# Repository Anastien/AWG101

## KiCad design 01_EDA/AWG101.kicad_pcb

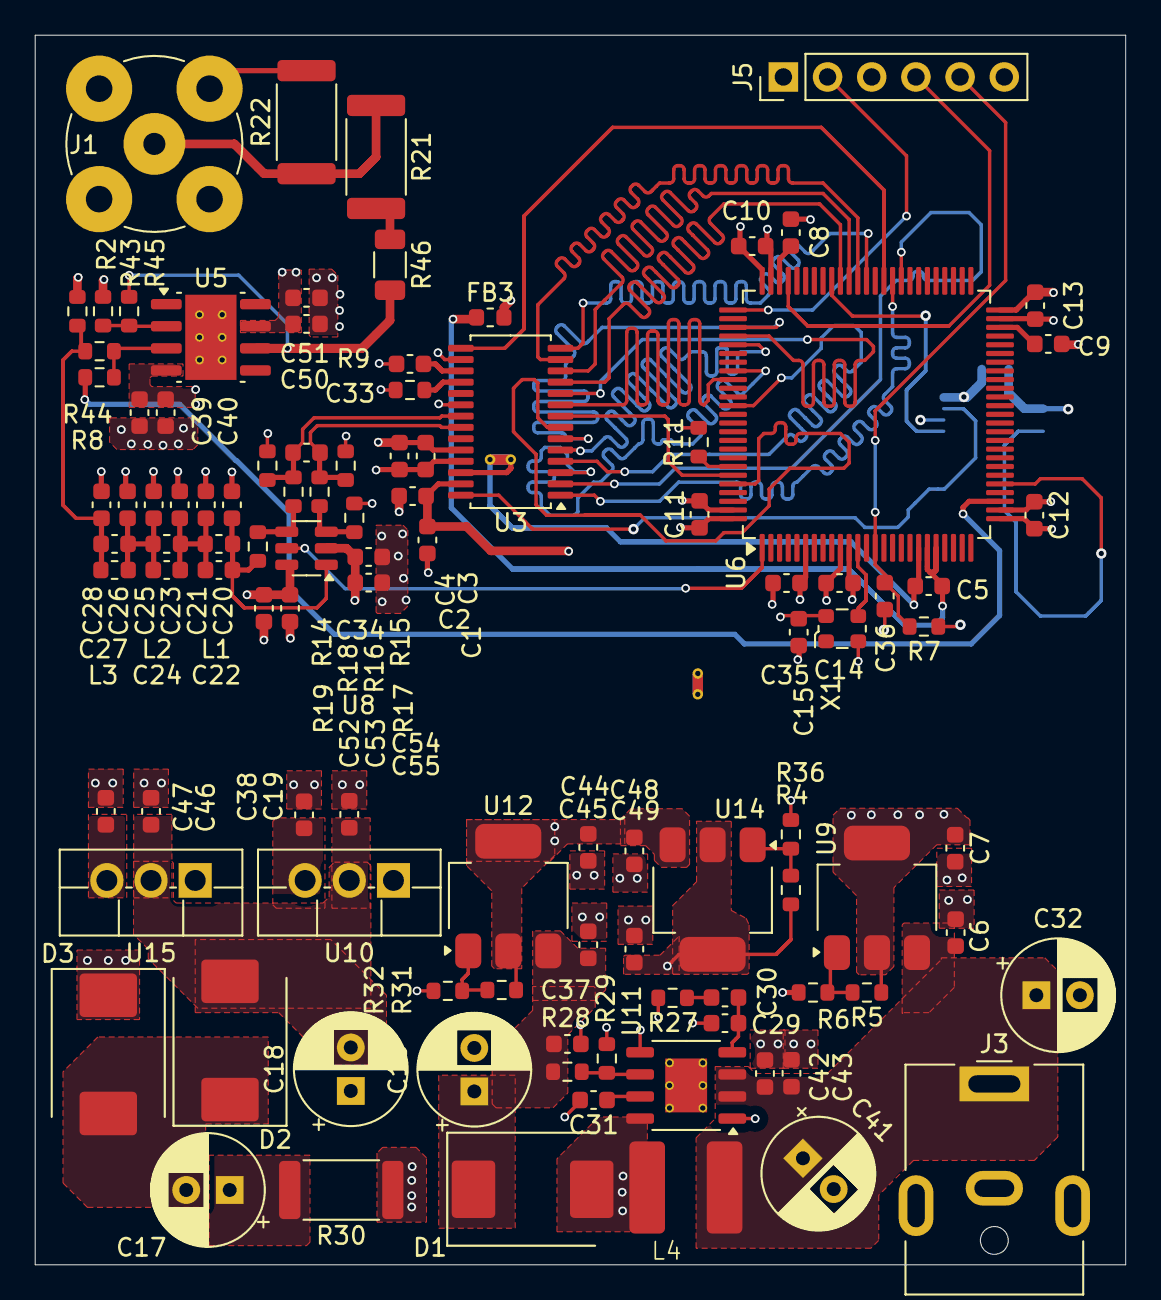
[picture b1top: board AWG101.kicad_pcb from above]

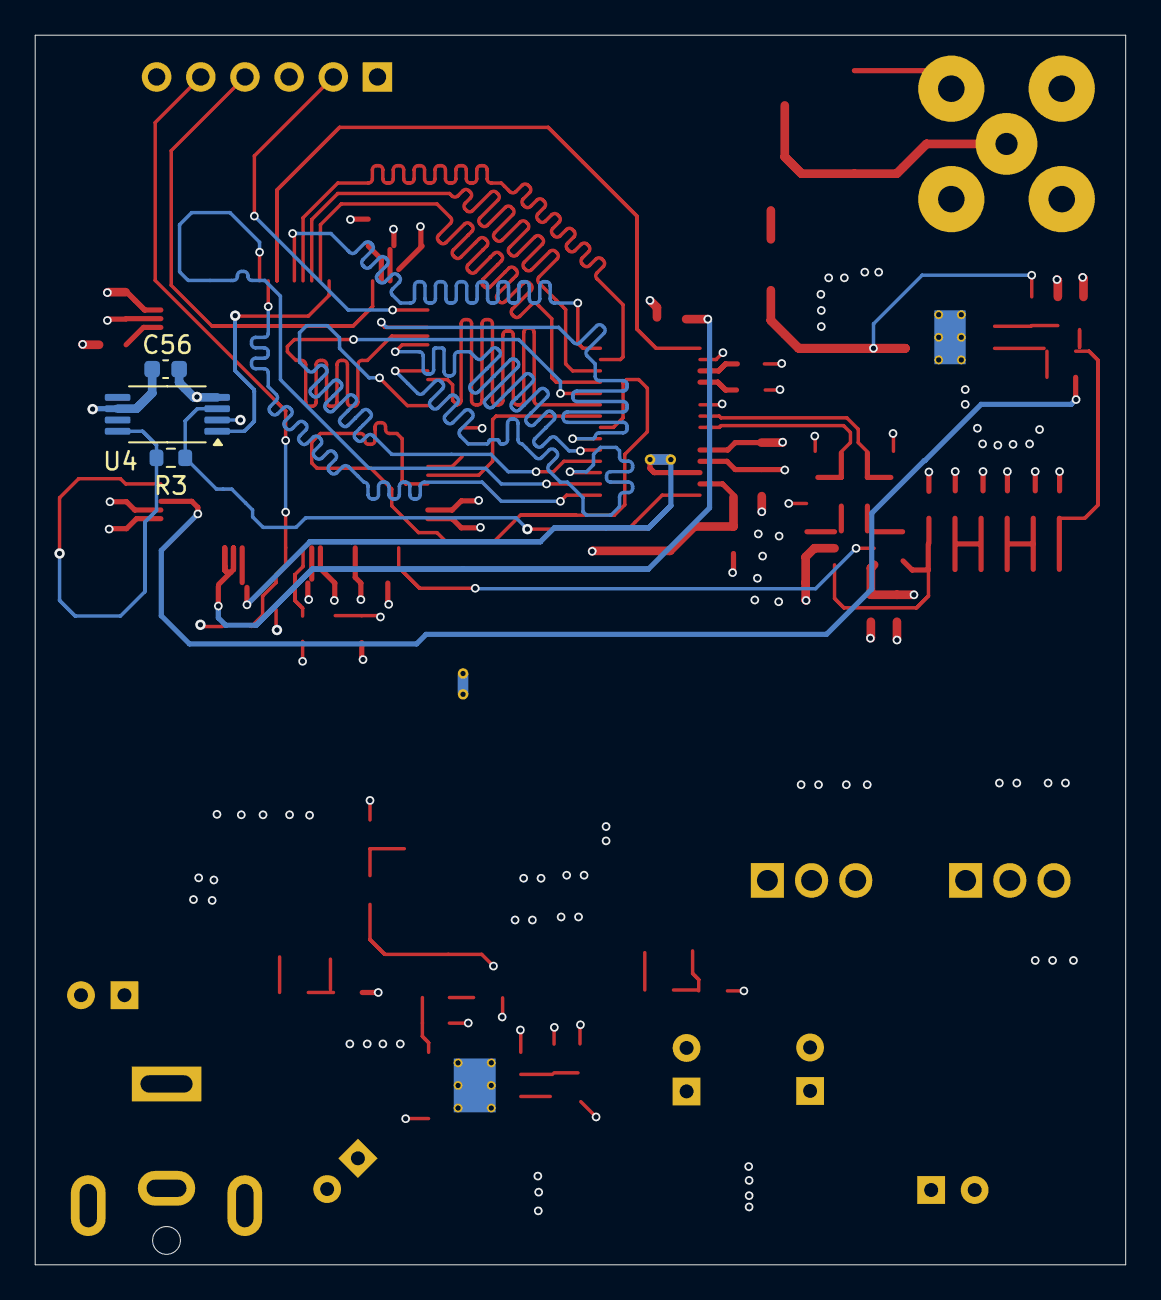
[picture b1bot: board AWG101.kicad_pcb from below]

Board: 4 copper layers, 62.7 x 70.7 mm, 109 parts (3 on the bottom side), 64 nets.

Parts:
C1, C2, C3, C4, C8, C9: 2.2U; C_0603_1608Metric
C5, C35: 4.7U; C_0603_1608Metric
C6, C7, C19, C37, C38, C39, C40, C42, C44, C45, C46, C47, C48, C49, C50, C51, C52, C53, C54, C55: 10u; C_0603_1608Metric
C10, C11, C12, C13, C14, C15, C36, C56: 0.1U; C_0603_1608Metric
C16, C17, C18, C32, C41: 120u; CP_Radial_D6.3mm_P2.50mm
C20, C28: 22pF; C_0603_1608Metric
C21, C25: 27pF; C_0603_1608Metric
C22, C24, C27: 9.1pF; C_0603_1608Metric
C23, C26: 91pF; C_0603_1608Metric
C29: 47p; C_0603_1608Metric
C30: 2.2n; C_0603_1608Metric
C31: 10n; C_0603_1608Metric
C33: 4.5pF; C_0603_1608Metric
C34: 10nF; C_0603_1608Metric
C43: 1u; C_0603_1608Metric
D1, D2, D3: SS34; D_SMC
FB3: FerriteBead; L_0603_1608Metric
J1: 112404; BNC_TEConnectivity_1478204_Vertical
J3: Jack-DC; BarrelJack_CUI_PJ-063AH_Horizontal
J5: PinHeader_1x06_P2.54mm_Vertical
L1, L3: 150nH; L_0603_1608Metric
L2: 250nH; L_0603_1608Metric
L4: 6.8u; OWINR6045-6R8
NT1, NT2: NetTie_2; NetTie-2_THT_Pad0.3mm
R2, R8, R17, R43, R44, R45: 35.7; R_0603_1608Metric
R3: 0; R_0603_1608Metric
R4, R6, R29, R32: 10k; R_0603_1608Metric
R5: 6.04k; R_0603_1608Metric
R7, R11: 10K; R_0603_1608Metric
R9: 49.9; R_0603_1608Metric
R14: 31.6; R_0603_1608Metric
R15: 53.6; R_0603_1608Metric
R16: 10.7; R_0603_1608Metric
R18: 221; R_0603_1608Metric
R19: 402; R_0603_1608Metric
R21, R22: 35.7; R_2512_6332Metric
R27: 51k; R_0603_1608Metric
R28: 93.1k; R_0603_1608Metric
R30: 1; R_2512_6332Metric
R31: 1.15k; R_0603_1608Metric
R36: 3.3k; R_0603_1608Metric
R46: 35.7; R_1206_3216Metric
U3: MXT2144; TSSOP-28_4.4x9.7mm_P0.65mm
U4: TSSOP-8_4.4x3mm_P0.65mm
U5: THS3095DDA; Texas_R-PDSO-G8_EP2.95x4.9mm_Mask2.4x3.1mm_ThermalVias
U6: STM32H723VGT6; LQFP-100_14x14mm_P0.5mm
U8: OPA695IDBVR; SOT-23-6
U9, U12, U14: LM1117MP-ADJ; SOT-223-3_TabPin2
U10: L7905; TO-220F-3_Vertical
U11: PAM2421AECADJR; HSOP-8-1EP_3.9x4.9mm_P1.27mm_EP2.41x3.1mm_ThermalVias
U15: L7912; TO-220F-3_Vertical
X1: ECS-TXO-2520MV-100-AN-TR; Oscillator_SMD_ECS_2520MV-xxx-xx-4Pin_2.5x2.0mm

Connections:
+3.3VLDO: C1.1, C2.1, C7.1, C10.1, C11.1, C12.1, C13.1, C14.1, C15.1, C35.1, C56.1, FB3.2, J5.1 (VDD), R5.1, R7.1, U3.27 (DVDD), U4.2 (1G), U4.6 (V_{DD}), U6.6 (VBAT), U6.11 (VDD), U6.27 (VDD), U6.50 (VDD), U6.75 (VDD), U6.100 (VDD), U9.2 (VO), X1.4 (VDD)
+3V3A: C3.1, C4.1, C5.1, FB3.1, U3.24 (AVDD), U6.20 (VREF+), U6.21 (VDDA)
+5VLDO: C49.1, C52.1, C53.1, R36.1, U8.6 (V+), U14.2 (VO)
+12VLDO: C45.1, C48.1, C50.1, C51.1, R31.1, U5.7 (V+), U12.2 (VO), U14.3 (VI)
+13V: C16.1, C37.1, C44.1, D1.1 (K), R28.1, U12.3 (VI)
-5V_LDO: C38.2, C54.1, C55.1, U8.2 (V-), U10.3 (VO)
-12V_LDO: C39.1, C40.1, C47.2, U5.4 (V-), U15.3 (VO)
-13V: C18.2, C19.2, C46.2, D3.2 (A), U10.2 (VI), U15.2 (VI)
/AWG/10MHZ: U6.12 (PH0), X1.3 (OUT)
/AWG/695_EN: U6.1 (PE2), U8.5 (~DIS)
/AWG/2421_SW: D1.2 (A), L4.2, R30.1, U11.8 (SW)
/AWG/DAC_CLK: R3.1, U3.28 (CLK), U4.3 (Y0)
/AWG/DAC_EN: U3.15 (SLEEP), U6.61 (PD14)
/AWG/DAC_SE: C20.1, C22.1, L1.1, R19.1, U8.1
/AWG/DAC_SE_FLT: C27.2, C28.1, L3.2, R2.1, R44.2
/AWG/IOUT_N: C34.1, R14.1, R18.2, U3.21 (IOUTB)
/AWG/IOUT_P: C34.2, R15.1, R16.2, U3.22 (IOUTA)
/AWG/MCO1: U4.1 (CLKIN), U6.67 (PA8)
/AWG/NRST: C36.1, J5.5 (NRST), R7.2, U6.14 (NRST)
/AWG/OFFSET: R8.2, U6.28 (PA4)
/AWG/PSSI_CLK: R3.2, U4.8 (Y3), U6.30 (PA6)
/AWG/PSSI_D0: U3.14 (D0), U6.63 (PC6)
/AWG/PSSI_D1: U3.13 (D1), U6.64 (PC7)
/AWG/PSSI_D2: U3.12 (D2), U6.65 (PC8)
/AWG/PSSI_D3: U3.11 (D3), U6.66 (PC9)
/AWG/PSSI_D4: U3.10 (D4), U6.79 (PC11)
/AWG/PSSI_D5: U3.9 (D5), U6.84 (PD3)
/AWG/PSSI_D6: U3.8 (D6), U6.95 (PB8)
/AWG/PSSI_D7: U3.7 (D7), U6.96 (PB9)
/AWG/PSSI_D8: U3.6 (D8), U6.78 (PC10)
/AWG/PSSI_D9: U3.5 (D9), U6.80 (PC12)
/AWG/PSSI_D10: U3.4 (D10), U6.87 (PD6)
/AWG/PSSI_D11: U3.3 (D11), U6.83 (PD2)
/AWG/PSSI_D12: U3.2 (D12), U6.59 (PD12)
/AWG/PSSI_D13: U3.1 (D13), U6.60 (PD13)
/AWG/SWCLK: J5.2 (SWCLK), U6.76 (PA14(JTCK)
/AWG/SWDIO: J5.4 (SWDIO), U6.72 (PA13(JTMS)
/AWG/S_OUT: R21.2, R46.1
AGND: C3.2, C4.2, C5.2, C20.2, C21.2, C23.2, C25.2, C26.2, C28.2, C33.2, C39.2, C40.2, C50.2, C51.2, C52.2, C53.2, C54.2, C55.2, J1.2 (Ext), NT1.2, R2.2, R9.1, R14.2, R15.2, R17.1, R22.2, R43.2, U3.16 (REFLO), U3.20 (AGND), U3.25 (MODE), U5.9 (EP), U6.19 (VSSA)
DGND: C1.2, C2.2, C8.2, C9.2, C10.2, C11.2, C12.2, C13.2, C14.2, C15.2, C35.2, C36.2, C56.2, J5.3 (GND), NT1.1, NT2.1, R11.2, U3.26 (DGND), U4.4 (GND), U6.10 (VSS), U6.26 (VSS), U6.49 (VSS), U6.74 (VSS), U6.99 (VSS), X1.2 (GND)
unnamed: C17.1, R30.2
unnamed: C21.1, C22.2, C23.1, C24.1, L1.2, L2.1
unnamed: C24.2, C25.1, C26.1, C27.1, L2.2, L3.1
unnamed: C30.2, R27.1
unnamed: C17.2, D2.2 (A), D3.1 (K)
unnamed: J1.1 (In), R21.1, R22.1
unnamed: R45.1, R46.2, U5.6
unnamed: R9.2, U3.18 (FS_ADJ)
unnamed: C33.1, U3.17 (REFIO)
unnamed: R8.1, R44.1, U5.3 (+)
unnamed: R43.1, R45.2, U5.2 (-)
unnamed: R11.1, U6.94 (BOOT0)
unnamed: R16.1, R17.2, U8.3 (+)
unnamed: R18.1, R19.2, U8.4 (-)
unnamed: R5.2, R6.2, U9.1 (ADJ)
unnamed: C29.1, C30.1, U11.4 (COMP)
unnamed: R28.2, R29.1, U11.6 (FB)
unnamed: C31.1, U11.7 (SS)
unnamed: R31.2, R32.2, U12.1 (ADJ)
unnamed: R4.2, R36.2, U14.1 (ADJ)
PGND: C6.2, C7.2, C16.2, C18.1, C19.1, C29.2, C31.2, C32.2, C37.2, C38.1, C41.2, C42.2, C43.1, C44.2, C45.2, C46.1, C47.1, C48.2, C49.2, D2.1 (K), J3.2, NT2.2, R4.1, R6.1, R27.2, R29.2, R32.1, U10.1 (GND), U11.1 (PGND), U11.5 (AGND), U15.1 (GND)
VCAP1: C9.1, U6.48 (VCAP)
VCAP2: C8.1, U6.73 (VCAP)
VIN: C6.1, C32.1, C41.1, C42.1, C43.2, J3.1, L4.1, U9.3 (VI), U11.2 (VIN), U11.3 (EN)

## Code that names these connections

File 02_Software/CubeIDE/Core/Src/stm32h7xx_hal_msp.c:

/* USER CODE BEGIN Header */
/**
  ******************************************************************************
  * @file         stm32h7xx_hal_msp.c
  * @brief        This file provides code for the MSP Initialization
  *               and de-Initialization codes.
  ******************************************************************************
  * @attention
  *
  * Copyright (c) 2024 STMicroelectronics.
  * All rights reserved.
  *
  * This software is licensed under terms that can be found in the LICENSE file
  * in the root directory of this software component.
  * If no LICENSE file comes with this software, it is provided AS-IS.
  *
  ******************************************************************************
  */
/* USER CODE END Header */

/* Includes ------------------------------------------------------------------*/
#include "main.h"
/* USER CODE BEGIN Includes */

/* USER CODE END Includes */
extern DMA_HandleTypeDef hdma_pssi;

/* Private typedef -----------------------------------------------------------*/
/* USER CODE BEGIN TD */

/* USER CODE END TD */

/* Private define ------------------------------------------------------------*/
/* USER CODE BEGIN Define */

/* USER CODE END Define */

/* Private macro -------------------------------------------------------------*/
/* USER CODE BEGIN Macro */

/* USER CODE END Macro */

/* Private variables ---------------------------------------------------------*/
/* USER CODE BEGIN PV */

/* USER CODE END PV */

/* Private function prototypes -----------------------------------------------*/
/* USER CODE BEGIN PFP */

/* USER CODE END PFP */

/* External functions --------------------------------------------------------*/
/* USER CODE BEGIN ExternalFunctions */

/* USER CODE END ExternalFunctions */

/* USER CODE BEGIN 0 */

/* USER CODE END 0 */
/**
  * Initializes the Global MSP.
  */
void HAL_MspInit(void)
{

  /* USER CODE BEGIN MspInit 0 */

  /* USER CODE END MspInit 0 */

  __HAL_RCC_SYSCFG_CLK_ENABLE();

  /* System interrupt init*/

  /* USER CODE BEGIN MspInit 1 */

  /* USER CODE END MspInit 1 */
}

/**
  * @brief PSSI MSP Initialization
  * This function configures the hardware resources used in this example
  * @param hpssi: PSSI handle pointer
  * @retval None
  */
void HAL_PSSI_MspInit(PSSI_HandleTypeDef* hpssi)
{
  GPIO_InitTypeDef GPIO_InitStruct = {0};
  if(hpssi->Instance==PSSI)
  {
    /* USER CODE BEGIN PSSI_MspInit 0 */

    /* USER CODE END PSSI_MspInit 0 */
    /* Peripheral clock enable */
    __HAL_RCC_DCMI_PSSI_CLK_ENABLE();

    __HAL_RCC_GPIOE_CLK_ENABLE();
    __HAL_RCC_GPIOA_CLK_ENABLE();
    __HAL_RCC_GPIOC_CLK_ENABLE();
    __HAL_RCC_GPIOB_CLK_ENABLE();
    __HAL_RCC_GPIOD_CLK_ENABLE();
    /**PSSI GPIO Configuration
    PE4     ------> PSSI_D4
    PE5     ------> PSSI_D6
    PE6     ------> PSSI_D7
    PA4     ------> PSSI_DE
    PA5     ------> PSSI_D14
    PA6     ------> PSSI_PDCK
    PC5     ------> PSSI_D15
    PB13     ------> PSSI_D2
    PD12     ------> PSSI_D12
    PD13     ------> PSSI_D13
    PC6     ------> PSSI_D0
    PC7     ------> PSSI_D1
    PC9     ------> PSSI_D3
    PC10     ------> PSSI_D8
    PC12     ------> PSSI_D9
    PD2     ------> PSSI_D11
    PD3     ------> PSSI_D5
    PD6     ------> PSSI_D10
    PB7     ------> PSSI_RDY
    */
    GPIO_InitStruct.Pin = GPIO_PIN_4|GPIO_PIN_5|GPIO_PIN_6;
    GPIO_InitStruct.Mode = GPIO_MODE_AF_PP;
    GPIO_InitStruct.Pull = GPIO_NOPULL;
    GPIO_InitStruct.Speed = GPIO_SPEED_FREQ_LOW;
    GPIO_InitStruct.Alternate = GPIO_AF13_PSSI;
    HAL_GPIO_Init(GPIOE, &GPIO_InitStruct);

    GPIO_InitStruct.Pin = GPIO_PIN_4|GPIO_PIN_5|GPIO_PIN_6;
    GPIO_InitStruct.Mode = GPIO_MODE_AF_PP;
    GPIO_InitStruct.Pull = GPIO_NOPULL;
    GPIO_InitStruct.Speed = GPIO_SPEED_FREQ_LOW;
    GPIO_InitStruct.Alternate = GPIO_AF13_PSSI;
    HAL_GPIO_Init(GPIOA, &GPIO_InitStruct);

    GPIO_InitStruct.Pin = GPIO_PIN_5;
    GPIO_InitStruct.Mode = GPIO_MODE_AF_PP;
    GPIO_InitStruct.Pull = GPIO_NOPULL;
    GPIO_InitStruct.Speed = GPIO_SPEED_FREQ_LOW;
    GPIO_InitStruct.Alternate = GPIO_AF4_PSSI;
    HAL_GPIO_Init(GPIOC, &GPIO_InitStruct);

    GPIO_InitStruct.Pin = GPIO_PIN_13|GPIO_PIN_7;
    GPIO_InitStruct.Mode = GPIO_MODE_AF_PP;
    GPIO_InitStruct.Pull = GPIO_NOPULL;
    GPIO_InitStruct.Speed = GPIO_SPEED_FREQ_LOW;
    GPIO_InitStruct.Alternate = GPIO_AF13_PSSI;
    HAL_GPIO_Init(GPIOB, &GPIO_InitStruct);

    GPIO_InitStruct.Pin = GPIO_PIN_12|GPIO_PIN_13|GPIO_PIN_2|GPIO_PIN_3
                          |GPIO_PIN_6;
    GPIO_InitStruct.Mode = GPIO_MODE_AF_PP;
    GPIO_InitStruct.Pull = GPIO_NOPULL;
    GPIO_InitStruct.Speed = GPIO_SPEED_FREQ_LOW;
    GPIO_InitStruct.Alternate = GPIO_AF13_PSSI;
    HAL_GPIO_Init(GPIOD, &GPIO_InitStruct);

    GPIO_InitStruct.Pin = GPIO_PIN_6|GPIO_PIN_7|GPIO_PIN_9|GPIO_PIN_10
                          |GPIO_PIN_12;
    GPIO_InitStruct.Mode = GPIO_MODE_AF_PP;
    GPIO_InitStruct.Pull = GPIO_NOPULL;
    GPIO_InitStruct.Speed = GPIO_SPEED_FREQ_LOW;
    GPIO_InitStruct.Alternate = GPIO_AF13_PSSI;
    HAL_GPIO_Init(GPIOC, &GPIO_InitStruct);

    /* PSSI DMA Init */
    /* PSSI Init */
    hdma_pssi.Instance = DMA1_Stream0;
    hdma_pssi.Init.Request = DMA_REQUEST_DCMI_PSSI;
    hdma_pssi.Init.Direction = DMA_PERIPH_TO_MEMORY;
    hdma_pssi.Init.PeriphInc = DMA_PINC_DISABLE;
    hdma_pssi.Init.MemInc = DMA_MINC_ENABLE;
    hdma_pssi.Init.PeriphDataAlignment = DMA_PDATAALIGN_WORD;
    hdma_pssi.Init.MemDataAlignment = DMA_MDATAALIGN_WORD;
    hdma_pssi.Init.Mode = DMA_NORMAL;
    hdma_pssi.Init.Priority = DMA_PRIORITY_LOW;
    hdma_pssi.Init.FIFOMode = DMA_FIFOMODE_DISABLE;
    if (HAL_DMA_Init(&hdma_pssi) != HAL_OK)
    {
      Error_Handler();
    }

    /* Several peripheral DMA handle pointers point to the same DMA handle.
     Be aware that there is only one channel to perform all the requested DMAs. */
    __HAL_LINKDMA(hpssi,hdmarx,hdma_pssi);
    __HAL_LINKDMA(hpssi,hdmatx,hdma_pssi);

    /* USER CODE BEGIN PSSI_MspInit 1 */

    /* USER CODE END PSSI_MspInit 1 */

  }

}

/**
  * @brief PSSI MSP De-Initialization
  * This function freeze the hardware resources used in this example
  * @param hpssi: PSSI handle pointer
  * @retval None
  */
void HAL_PSSI_MspDeInit(PSSI_HandleTypeDef* hpssi)
{
  if(hpssi->Instance==PSSI)
  {
    /* USER CODE BEGIN PSSI_MspDeInit 0 */

    /* USER CODE END PSSI_MspDeInit 0 */
    /* Peripheral clock disable */
    __HAL_RCC_DCMI_PSSI_CLK_DISABLE();

    /**PSSI GPIO Configuration
    PE4     ------> PSSI_D4
    PE5     ------> PSSI_D6
    PE6     ------> PSSI_D7
    PA4     ------> PSSI_DE
    PA5     ------> PSSI_D14
    PA6     ------> PSSI_PDCK
    PC5     ------> PSSI_D15
    PB13     ------> PSSI_D2
    PD12     ------> PSSI_D12
    PD13     ------> PSSI_D13
    PC6     ------> PSSI_D0
    PC7     ------> PSSI_D1
    PC9     ------> PSSI_D3
    PC10     ------> PSSI_D8
    PC12     ------> PSSI_D9
    PD2     ------> PSSI_D11
    PD3     ------> PSSI_D5
    PD6     ------> PSSI_D10
    PB7     ------> PSSI_RDY
    */
    HAL_GPIO_DeInit(GPIOE, GPIO_PIN_4|GPIO_PIN_5|GPIO_PIN_6);

    HAL_GPIO_DeInit(GPIOA, GPIO_PIN_4|GPIO_PIN_5|GPIO_PIN_6);

    HAL_GPIO_DeInit(GPIOC, GPIO_PIN_5|GPIO_PIN_6|GPIO_PIN_7|GPIO_PIN_9
                          |GPIO_PIN_10|GPIO_PIN_12);

    HAL_GPIO_DeInit(GPIOB, GPIO_PIN_13|GPIO_PIN_7);

    HAL_GPIO_DeInit(GPIOD, GPIO_PIN_12|GPIO_PIN_13|GPIO_PIN_2|GPIO_PIN_3
                          |GPIO_PIN_6);

    /* PSSI DMA DeInit */
    HAL_DMA_DeInit(hpssi->hdmarx);
    HAL_DMA_DeInit(hpssi->hdmatx);
    /* USER CODE BEGIN PSSI_MspDeInit 1 */

    /* USER CODE END PSSI_MspDeInit 1 */
  }

}

/* USER CODE BEGIN 1 */

/* USER CODE END 1 */

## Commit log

2025-08-06 Init.
